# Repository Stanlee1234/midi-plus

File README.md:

# midi-plus

A capacitive touch MIDI keyboard featuring 12 chromatic keys, low-profile mechanical switches, slide potentiometers, rotary encoder navigation, and a bespoke high-precision mechanical enclosure.

---

## ✨ Features

- **12 Capacitive Touch Keys**: Full 1-octave chromatic piano layout (7 naturals + 5 accidentals) etched into the PCB surface for lightning-fast touch sensing.
- **3 Kailh Choc Low-Profile Switches**: Tactile buttons (`SW1`, `SW2`, `SW3`) with reverse-mount SK6812 RGB LED backlighting for mode switching, octave transposition, or preset selection.
- **EC11 Rotary Encoder**: Multi-turn rotary encoder with integrated push button (`SW4`) for parameter scrubbing and menu selection.
- **Dual Bourns Slide Potentiometers**: 15mm stroke faders (`RV1`, `RV2`) for pitch bend, modulation, filter cutoff, or volume control.
- **Raspberry Pi Pico (RP2040)**: Core microcontroller providing USB-MIDI connectivity and capacitive sensing via an onboard resistor ladder network (`R1`–`R12`).
- **Precision 3D Enclosure**: Custom two-piece clamshell console enclosure engineered in CAD (`build123d` / OpenCASCADE) with an ergonomic 3.95° incline, zero-screw PCB clamping, and tongue-and-groove alignment.

---

## 🎛️ 3D Enclosure STEP Files

The enclosure CAD models are located in [`Case3D/`](Case3D/):

- **[Case + PCB Master Assembly (`midi_plus_case_assembled.step`)](Case3D/midi_plus_case_assembled.step)**: Full assembly with the KiCad PCB seated inside the enclosure.
- **[Complete Case (`midi_plus_case.step`)](Case3D/midi_plus_case.step)**: Top Shell and Bottom Shell mated together.
- **[Top Console Shell (`midi_plus_top_shell.step`)](Case3D/midi_plus_top_shell.step)**: Upper faceplate with ergonomic console slope, capacitive key window, switch wells, and slider slots.
- **[Bottom Base Shell (`midi_plus_bottom_shell.step`)](Case3D/midi_plus_bottom_shell.step)**: Lower enclosure with internal PCB support shelf, countersunk screw bores, and non-slip foot pockets.
- **[Enclosure Documentation (`Case3D/README.md`)](Case3D/README.md)**: Mechanical tolerances, stackup specifications, and assembly instructions.

---

## 📂 Repository Structure

```
midi-plus/
├── BOM.csv                       # Bill of materials
├── JOURNAL.md                    # Hardware development log
├── README.md                     # Project overview and specifications
├── KiCad/                        # KiCad PCB and schematic files
│   ├── KiCad.kicad_pcb           # PCB layout
│   ├── KiCad.kicad_sch           # Schematic
│   ├── pcb.step                  # KiCad exported PCB 3D STEP model
│   └── ModelsAndSymbols/         # 3D component STEP models (Bourns, EC11)
└── Case3D/                       # Precision Mechanical Enclosure
    ├── README.md                 # Enclosure specifications and assembly guide
    ├── generate_case.py          # Parametric CAD generator (build123d)
    ├── midi_plus_case_assembled.step  # Master assembly (Case + PCB)
    ├── midi_plus_case.step            # Complete two-piece case
    ├── midi_plus_top_shell.step       # Top console shell
    └── midi_plus_bottom_shell.step    # Bottom base shell
```

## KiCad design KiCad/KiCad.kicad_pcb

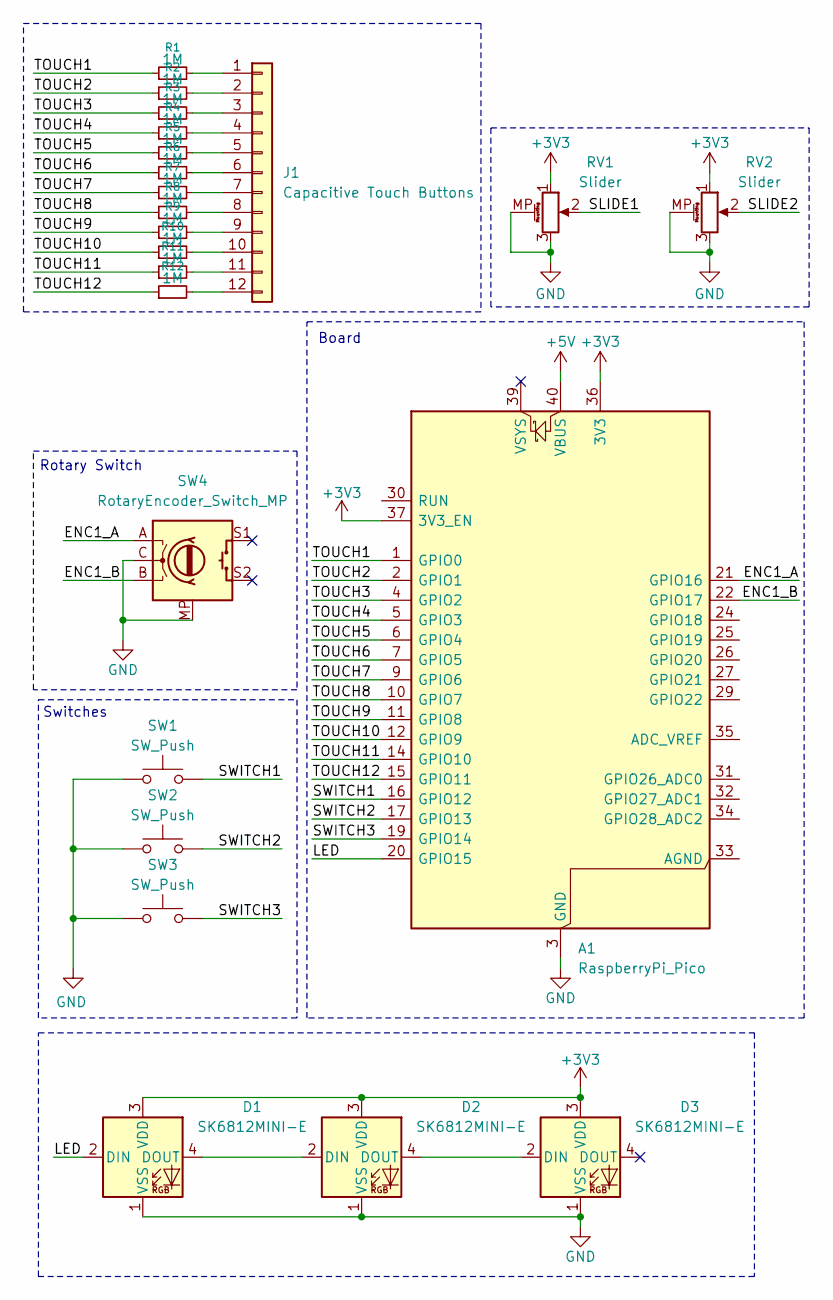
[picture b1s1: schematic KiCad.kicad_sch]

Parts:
A1: RaspberryPi_Pico; RaspberryPi_Pico_Common_Unspecified
D1, D2, D3: SK6812MINI-E; LED_SK6812MINI-E_3.2x2.8mm_P1.5mm_ReverseMount
J1: Capacitive Touch Buttons; Capacitive Keys_Aligned
R1, R2, R3, R4, R5, R6, R7, R8, R9, R10, R11, R12: 1M; R_Axial_DIN0207_L6.3mm_D2.5mm_P10.16mm_Horizontal
RV1, RV2: Slider; Potentiometer_Bourns_PTA1543_Single_Slide
SW1, SW2, SW3: SW_Push; Kailh Choc Low-Profile Switches
SW4: RotaryEncoder_Switch_MP; RotaryEncoder_Alps_EC11E-Switch_Vertical_H20mm

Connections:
+3V3: A1.36 (3V3), A1.37 (3V3_EN), D1.3 (VDD), D2.3 (VDD), D3.3 (VDD), RV1.1, RV2.1
+5V: A1.40 (VBUS)
/ENC1_A: A1.21 (GPIO16), SW4.A
/ENC1_B: A1.22 (GPIO17), SW4.B
/LED: A1.20 (GPIO15), D1.2 (DIN)
/SLIDE1: RV1.2
/SLIDE2: RV2.2
/SWITCH1: A1.16 (GPIO12), SW1.2
/SWITCH2: A1.17 (GPIO13), SW2.2
/SWITCH3: A1.19 (GPIO14), SW3.2
/TOUCH1: A1.1 (GPIO0), R1.1
/TOUCH2: A1.2 (GPIO1), R2.1
/TOUCH3: A1.4 (GPIO2), R3.1
/TOUCH4: A1.5 (GPIO3), R4.1
/TOUCH5: A1.6 (GPIO4), R5.1
/TOUCH6: A1.7 (GPIO5), R6.1
/TOUCH7: A1.9 (GPIO6), R7.1
/TOUCH8: A1.10 (GPIO7), R8.1
/TOUCH9: A1.11 (GPIO8), R9.1
/TOUCH10: A1.12 (GPIO9), R10.1
/TOUCH11: A1.14 (GPIO10), R11.1
/TOUCH12: A1.15 (GPIO11), R12.1
GND: A1.3 (GND), A1.8 (GND), A1.13 (GND), A1.18 (GND), A1.23 (GND), A1.28 (GND), A1.38 (GND), D1.1 (VSS), D2.1 (VSS), D3.1 (VSS), RV1.3, RV1.MP (MountPin), RV2.3, RV2.MP (MountPin), SW1.1, SW2.1, SW3.1, SW4.C, SW4.MP
unnamed: D1.4 (DOUT), D2.2 (DIN)
unnamed: D2.4 (DOUT), D3.2 (DIN)
unnamed: J1.1, R1.2
unnamed: J1.2, R2.2
unnamed: J1.3, R3.2
unnamed: J1.4, R4.2
unnamed: J1.5, R5.2
unnamed: J1.6, R6.2
unnamed: J1.7, R7.2
unnamed: J1.8, R8.2
unnamed: J1.9, R9.2
unnamed: J1.10, R10.2
unnamed: J1.11, R11.2
unnamed: J1.12, R12.2

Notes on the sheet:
Board
Switches
Rotary Switch

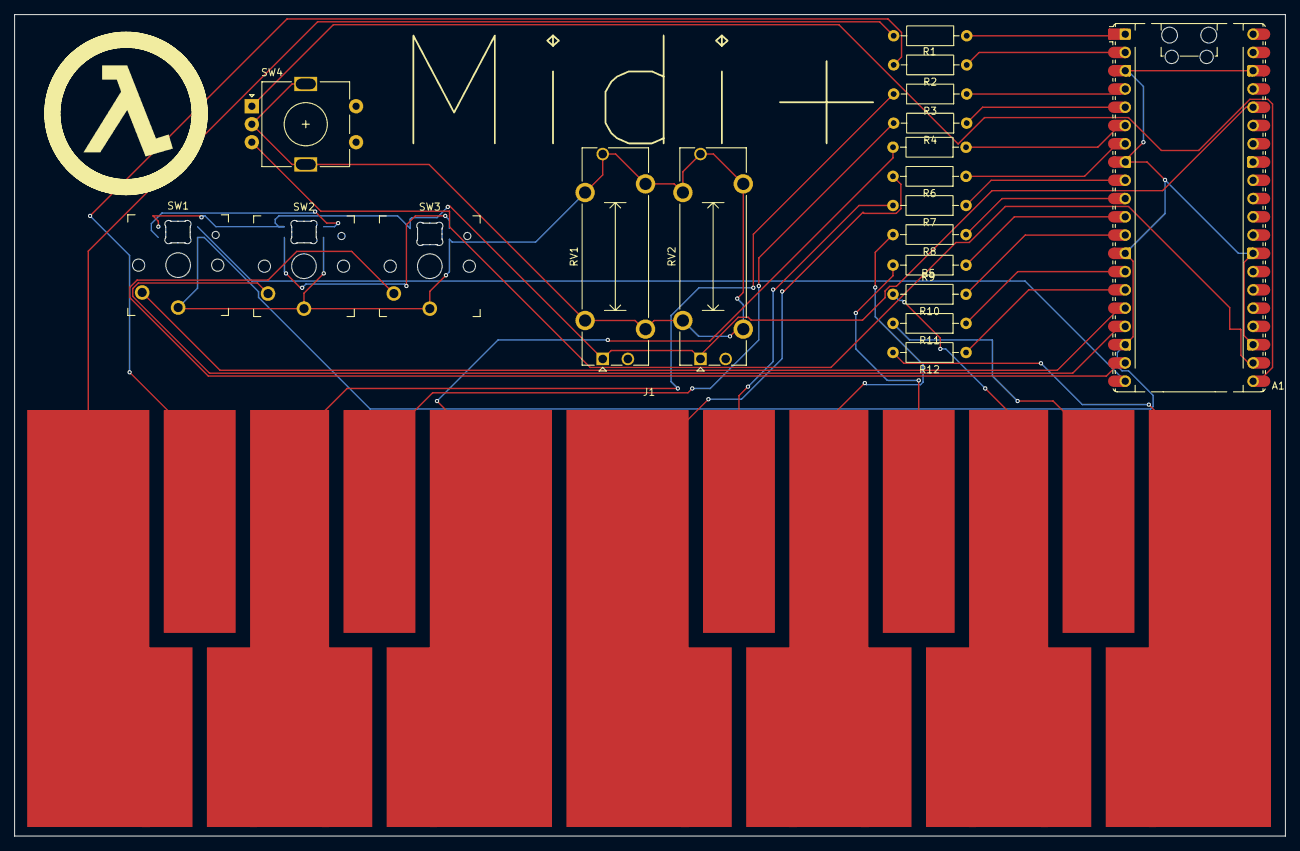
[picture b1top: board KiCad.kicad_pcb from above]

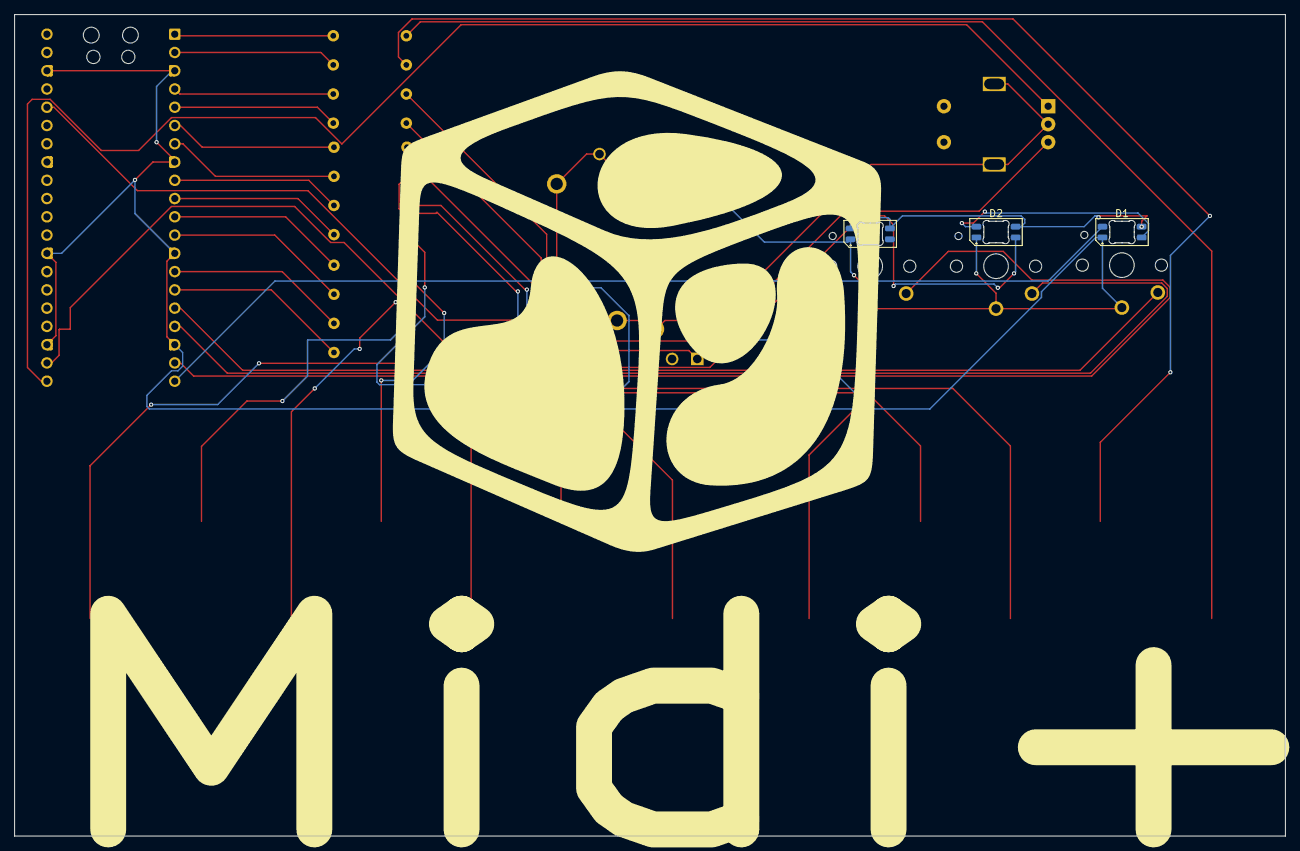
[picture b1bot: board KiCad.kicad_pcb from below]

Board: 2 copper layers, 176.8 x 114.2 mm, 23 parts (3 on the bottom side), 34 nets.

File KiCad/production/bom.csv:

Designator,Footprint,Quantity,Value,LCSC Part #
A1,RaspberryPi_Pico_Common_Unspecified,1,RaspberryPi_Pico,
"D1, D2, D3",LED_SK6812MINI-E_3.2x2.8mm_P1.5mm_ReverseMount,3,SK6812MINI-E,
J1,Capacitive Keys_Aligned,1,Capacitive Touch Buttons,
"R1, R10, R11, R12, R2, R3, R4, R5, R6, R7, R8, R9",R_Axial_DIN0207_L6.3mm_D2.5mm_P10.16mm_Horizontal,12,1M,
"RV1, RV2",Potentiometer_Bourns_PTA1543_Single_Slide,2,Slider,
"SW1, SW2, SW3",Kailh Choc Low-Profile Switches,3,SW_Push,
SW4,RotaryEncoder_Alps_EC11E-Switch_Vertical_H20mm,1,RotaryEncoder_Switch_MP,
